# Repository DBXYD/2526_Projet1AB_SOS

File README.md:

# 2526_Projet1AB_SOS
## Introduction
### 1.1 Contexte et Problématique
Dans le cadre de la gestion logistique des laboratoires de l'ENSEA, le suivi précis et rigoureux des composants électroniques constitue un défi quotidien. Actuellement, l'inventaire repose sur un référencement manuel via un fichier Excel, et le stockage physique est réparti dans des boîtes de dimensions variables.
Ce mode de gestion présente plusieurs limites :

- Erreurs d'indexation : Risque élevé d'oublis ou de doubles saisies lors d'une mise à jour des stocks.
- Perte de traçabilité spatiale : Difficulté à localiser physiquement les boîtes suite à des déplacements ou réorganisations.
- Asynchronisme des données : Décalage temporel entre le mouvement réel d'un composant et sa mise à jour logicielle.

### 1.2 Objectifs du Projet SOS
Le projet SOS (Stock Organizer Scan) vise à concevoir un système embarqué de numérisation basé sur la technologie RFID (Radio Frequency Identification).
Chaque boîte de rangement se voit attribuer un tag RFID unique. Le dispositif SOS lit et écrit ces puces pour associer un contenant physique à ses données logistiques :
- Le MPN (Manufacturer Part Number) : référence exacte du constructeur
- SKU (Stock Keeping Unit) : code interne d'identification du stock
- LocalisationSalle précise au sein des différents tiroclasses de l'ENSEA
- Quantité exacte d'exemplaires restants

### 1.3 Solution mise en œuvre
Le projet s'articule autour de deux parties :

1) [Hardware](./Hardware) : Une carte électronique sur mesure intégrant une carte électronique sur mesure intégrant un microcontrôleur basse
consommation STM32L4, un lecteur RFID communiquant via bus SPI matériel, et une interface USB-C assurant à la fois l’alimentation et l’échange de données haut débit.

3) [Software](./Software) : Une interface utilisateur développée en Python, permettant aux techniciens d'interagir avec la base de données.

## 2. Analyse détaillée des blocs fonctionnels
Le schématique du système SOS (Stock Organizer Scan) est structuré de manière ri-
goureuse en blocs fonctionnels distincts.

### 2.1 Bloc Alimentation (Power Supply)

Ce bloc assure la conversion et la régulation de l'énergie nécessaire aux différents composants.

- Composants identifiés :
  - Régulateur LDO :  BU33SD5WG-TR (5 V → 3.3 V)
  - Condensateurs : C1 (1 μF) et C2 (1 μF)
  - Interrupteur : SW_SPDT (SW1)
  - LEDs indicatrices : D1 et D2 avec résistances associées R3 (3.4 kΩ) et R4 (1.6 kΩ)

- Justification des choix :
  - BU33SD5WG-TR : Ce régulateur (LDO) est particulièrement adapté pour abaisser le 5V issu de l’USB vers le rail 3.3 V. Son boîtier compact minimise l’empreinte au sol. De plus, sa capacité en courant ici est largement suffisante pour alimenter simultanément notre microcontrôleur STM32 et le lecteur RFID.

  - C1 et C2 (1 μF) : Placés en découplage direct sur l’entrée et la sortie du LDO conformément aux spécifications du constructeur. Ils stabilisent la tension ici.
  - SW1 (SW_SPDT) : Permet de couper l’alimentation de la carte sans avoir à débrancher physiquement le câble USB. Cela est plutôt intéressant d’un point de vue confort d’utilisation.

### 2.2 Bloc Port USB (USB-C)

L'interface USB-C gère le transfert de données et l'apport d'énergie principal.

- Composants identifiés :
  - Connecteur USB-C : J1 (Référence commerciale : 629722000214)
  - Protection ESD : U2 (USBLC6-2SC6)
  - Résistances de configuration : R1 (5.4 kΩ), R2 (5.1 kΩ) sur les lignes CC1/CC2
  - 
- Justification des choix :
  - Connecteur Molex USB-C : Nous avons opter ici pour USB-C et non un Micro-USB car
le premier est réversible et largement plus robustesse.
  - USBLC6-2SC6 : Réseau de diodes TVS bidirectionnel ultra-faible capacité dédié à la
protection des lignes D+ et D−. Cette protection est indispensable contre les décharges
électrostatiques (ESD) induites lorsque’un humaine manipule le connecteur USB manuellement.

### 2.3 Bloc STM32 (Microcontrôleur principal)

Le cœur logique du système repose sur le STM32L476RGTx (boîtier LQFP64) de STMicroelectronics. Composant central : STM32L476RGTx.

Ecosystème ENSEA : Il s’agit d’un composant sur lequel nous avons ulterieusrement eu a travaillé durant les séances de TD et TP surtout. SPI Matériel dispose de plusieurs bus SPI indépendants pour piloter à haute fréquence le lecteur RFID.

- Signaux notables :
  - SPI1_* → Liaison vers le lecteur RFID.
  - VCP_TX / VCP_RX → Interface UART pontée vers l’USB pour la communication avec le
script Python.
  - USB_DN / USB_DP → Lignes différentielles du bus USB physique.
  - SWDIO / SWCLK → Interface de programmation/débogage JTAG/SWD.
  - USR_LED_1 / USR_LED_2 → Indication d’état utilisateur (ex : scan réussi).
  - NRST / BOOT0 → Lignes de contrôle.
 
Remarque : Les condensateurs de découplage (C5 à C10, 100 nF) sont assignés individuellement à chaque broche d’alimentation VDD du STM32. Ils suppriment le bruit haute fréquence issu des commutations internes du coeur.

### 2.4 Bloc Lecteur RFID

Ce bloc gère l'acquisition des données des tags RFID attachés aux produits stockés.

- Interface SPI : Exploitation du bus à haute vitesse (jusqu’à 10 Mbit/s), réduisant la
latence lors de la lecture des identifiants.
- Compatibilité de tension : Fonctionnant sous 3.3 V, le composant fonctione directement
avec le STM32.
- Découplage local (C13,C14 - 1 μF) : Placés au plus près du circuit RFID pour pallier les
appels de courant violents générés par l’antenne lors de l’émission du champ magnétique
RF.

### 2.5 Bloc Connecteur SWD

Ce bloc offre un accès direct aux broches de débogage via une sonde externe de type ST-Link, pour le flashage et le débogage à chaud du microcontrôleur.

### 2.6 Boutons et signaux utilisateur

### 2.7 Trous de fixation (Mounting Pads)

Les quatre perçages H1 à H4 (MountingHole_Pad) garantissent la rigidité de l’intégration au sein d’un boîtier personnalisé.

## 3. Routage
Le passage du schéma théorique du [PCB](./PCB) permettant le tracé des pistes physiques impose le respect de contraintes géométriques et électromagnétiques strictes.

### 3.1 Réalisation Matérielle et Placements des blocs

La conception du circuit imprimé a abouti à une modélisation tridimensionnelle permettant de valider l’intégration mécanique des composants, l’accessibilité des connecteurs.

Le microcontrôleur STM32L476RGTx (boîtier LQFP64) occupe une position parfaitement centrale. Cette disposition permet une distribution homogène des pistes de signaux vers les différents périphériques, minimisant ainsi la longueur moyenne des pistes.

- Implantation des diffférents blocs :
  - Connecteur USB-C et Protection ESD : Placés au plus près du bord de la carte. L’alignement direct du circuit de protection TVS en entrée du connecteur garantit que les décharges électrostatiques sont immédiatement dérivées vers la masse avant de pouvoir se propager vers l’intérieur du circuit.
  - Connecteur d’extension RFID : Disposé sur la périphérie supérieure sous forme d’un connecteur femelle barrette, offrant une liaison mécanique et électrique stable pour le module MFRC522 tout en évitant les superpositions de composants.
  - Connecteur SWD (J2) : Isolé à droite afin de permettre un raccordement aisé de la sonde ST-Link lors des phases de flashage sans gêner l’accès au port USB principal.
  - Mounting Pads : la présence de quatre trous de fixation métallisés (Mounting Pads) répartis de manière symétrique aux quatre angles de la carte valide l’aptitude du prototype à être intégré de manière rigide au sein d’un boîtier de protection. L’espacement laissé libre autour de ces trous garantit le passage des têtes de vis sans risque d’écrasement ou de court-circuit sur les pistes environnantes.

## 4. Configuration des pins

Le microcontrôleur STM32L476RGTx (LQFP64) est configuré avec les affectations suivantes :

- Port A — SPI1 (NSS, SCK, MISO, MOSI), USB (DM, DP), VCP (TX, RX)
- Port B — RFID IRQ, boutons utilisateur (BTN_1, BTN_2), SWD, LEDs utilisateur
- Port C — OSC, LEDs, RFID RST
- Signaux de contrôle — NRST, BOOT0

## 5. Software
### 5.1 Firmware
La liaison entre le PC et le tag RFID à travers le PCB est gérée par du code en C, où on retrouve une séparation par composants. Le projet est construit de manière à pouvoir réutiliser des morceaux du code pour d’autres projets faisant intervenir des composants de celui-ci.\
Par la suite on détaillera seulement les fichiers contenant des fonctions écrites par nous, et non des fichiers générés par STM32CubeIDE lors de l'affectation des pins sur le .ioc (gpio, spi, usart,...).\

Dans le main.c se trouvent des appels aux fonctions d'initialisation et une boucle infinie où l'appel à test() de algo.c permet de tester des fonctionnalités en mode debuggeur.\
\
Le fichier rfid.c contient des fonctions ayant trait à la liaison SPI entre la STM32 et le lecteur RFID, et une structure permettant de définir les broches associées à un lecteur RFID. Cette dernière est initialisée grâce à la fonction RFID_init(hrfid, hspi, hspi_nss_port, hspi_nss_pin, rst_port, rst_pin). 

- void RFID_transmit(RFID_HandleTypeDef* hrfid, uint8_t* data, int size) transmet les données de data au tag et les y écrit;
- void RFID_receive(RFID_HandleTypeDef* hrfid, uint8_t* data, int size) lit les données du tag et les envoie au master en les stockant dans un buffer data.
- void RFID_transmit_receive(RFID_HandleTypeDef* hrfid, uint8_t* pTxData, uint8_t* pRxData, int size) fait les deux, l’un après l’autre.

Le fichier algo.c contient des fonctions rassemblant celles des autres fichiers, mettant ainsi bout à bout les différents éléments du PCB. Les fonctions read et write font alors intervenir le lecteur RFID et la liaison USART avec le PC. 

- void test() est utile pour la phase développement: elle aide à vérifier le fonctionnement de read(huart, hrfid, pdata, size) et write(huart, hrfid, pdata, size). On commence par lire le tag RFID, puis on y enregistre des données qu’on cherche enfin à retrouver en refaisant appel à read. 

- uint8_t SPI1_WriteRead(uint8_t data, SPI_HandleTypeDef hspi1) fait appel à RRFID_transmit_receive(hrfid, pTxData, pRxData, size). Elle est particulièrement utile dans les cas où ces deux actions doivent être effectuées l’une après l’autre. RFID_transmit_receive gère le délai de transmission. 

### 5.2 Interface Python
Pour assurer l’interface entre l’utilisateur et la carte électronique SOS, une application logicielle a été développée en Python qui était une condition nécéssaire dans notre projet. 
L’application s’appuie sur trois bibliothèques clés, assurant chacune un rôle pilier dans le traitement des données :
Le script Python s’appuie sur trois bibliothèques principales pour articuler ses différentes tâches. Elles sont structurées de la manière suivante :

- serial :
  - Rôle : Gestion de la couche de liaison série.
  - Utilité : Permet l’ouverture, la configuration et l’écoute du port COM virtuel (VCP) créé par le branchement USB-C du STM32. C’est elle qui intercepte le flux binaire.
    
- tkinter :
  - Rôle : Framework de construction d’Interface Homme-Machine (IHM).
  - Utilité : Bibliothèque standard de Python permettant de générer la fenêtre principale de l’application SOS, de positionner les boutons de contrôle et de mettre à jour dynamiquement les étiquettes de texte lors d’un scan.

- pandas :
  - Rôle : Manipulation et analyse de structures de données.
  - Utilité : Charge en mémoire le fichier tableur Excel faisant office de base de données d’inventaire de l’ENSEA. Elle permet d’effectuer des recherches indexées ultrarapides à partir d’un emplacement donné pour en extraire le MPN et le SKU.

Dans notre progremme Python, on retrouve les fonctions suivantes : 
- scan() :
  - Entrée : void
  - Rôle : Ouvre le canal de communication série USB-C avec le STM32.
  - Sortie : serial.Serial ou None : ser (instance de connexion)
- decode(data) :
  - Entrée : bytes : data
  - Rôle : Convertit les données en hexadécimal reçues en une listee de caractères utilisable.
  -Sortie : list[str,str,int,int,int] : location
- search_info(location) :
  - Entrée : list : location
  - Rôle : Requête de recherche au sein du fichier d’inventaire Excel 
  - Sortie : int : mpn, int : sku
- display_info(mpn, sku, location) :
  - Entrée : int : mpn, int : sku, list : location
  - Rôle : Met à jour dynamiquement l’interface graphique.
  - Sortie : NoneType : None
- read_data():
  - Entrée : void
  - Rôle : Suite à l'appui sur le bouton read, appelle les fonction scan, decode, search_info et display_info pour afficher SKU, MPN et localisation sur l'interface
  - Sortie : Nonetype : None
- write_loc():
  - Entrée : void
  - Rôle : demande à l'utilisateur la localisation à attribuer à la puce scannée 
  - Sortie : Nonetype : None
- display_value():
  - Entrée : void
  - Rôle : Suite à l'appui sur le bouton "done" (lorque l'utilisateur a entré la localisation et a terminé), convertit cette localisation en identifiant (locbytes) puis appelle la fonction assign_tag(loc_bytes)
  - Sortie : Nonetype : None
- assign_tag(loc_bytes):
  - Entrée : bytes loc_bytes
  - Rôle : Ouvre le canal de communication série USB-C avec le STM32 et envoie à la STM32 l'identifiant à attribuer à la puce.
  - Sortie : Nonetype : None
  
## 6. Question environnementale

A l'issue de notre projet nous avons finalement choisis la question : Votre projet recherche-t-il la rentabilité dans une perspective de viabilité financière ?

A cette question, nous y repondons *oui* et ce pour plusieurs raisons :
- **Gain de temps et d'organisation** : le système SOS permet aux techniciens de localiser instantanément les composants, réduisant les pertes de temps liées à la recherche manuelle en tiroir.
- **Économie d'argent important** : avec une actualisation automatique du système, nous pouvons éviter de recommander des composants déjà présents au sein de l'école.
- **Facilité de commande** : grâce au suivi précis des stocks (quantité, SKU, MPN), les réapprovisionnements sont déclenchés au bon moment, évitant les ruptures comme les sur-stocks inutiles.
- **"Le temps c'est de l'argent"** : chaque minute gagnée en gestion de stock est une minute réinvestie dans des tâches à plus forte valeur ajoutée.

En ce sens, le projet SOS s'inscrit pleinement dans une logique de rentabilité opérationnelle et de viabilité financière à long terme.

## Conslusion
Le projet SOS (Stock Organizer Scan) est, à ce stade, un projet en cours de développement dont on a malheuresement pas pu venir à bout. Cependant, nous avons pu faire une belle avancée : une carte électronique sur mesure intégrant un microcontrôleur STM32L4 et un lecteur RFID, couplée à une interface logicielle en Python, constitue une solution cohérente et pensée pour répondre à un besoin concret au sein de l'ENSEA.

Même inachevé, le projet démontre une réelle utilité : automatiser le suivi des composants électroniques, réduire les erreurs de gestion de stock et faciliter les commandes sont des apports directs pour les techniciens et les étudiants qui utilisent les tiroclasses au quotidien.

Ce projet nous a également permis de monter en compétences sur des technologies variées : conception PCB, communication SPI, développement logiciel et gestion de projet en équipe. Il constitue une base que d'autres promotions pourraient reprendre et faire évoluer vers un système pleinement opérationnel.

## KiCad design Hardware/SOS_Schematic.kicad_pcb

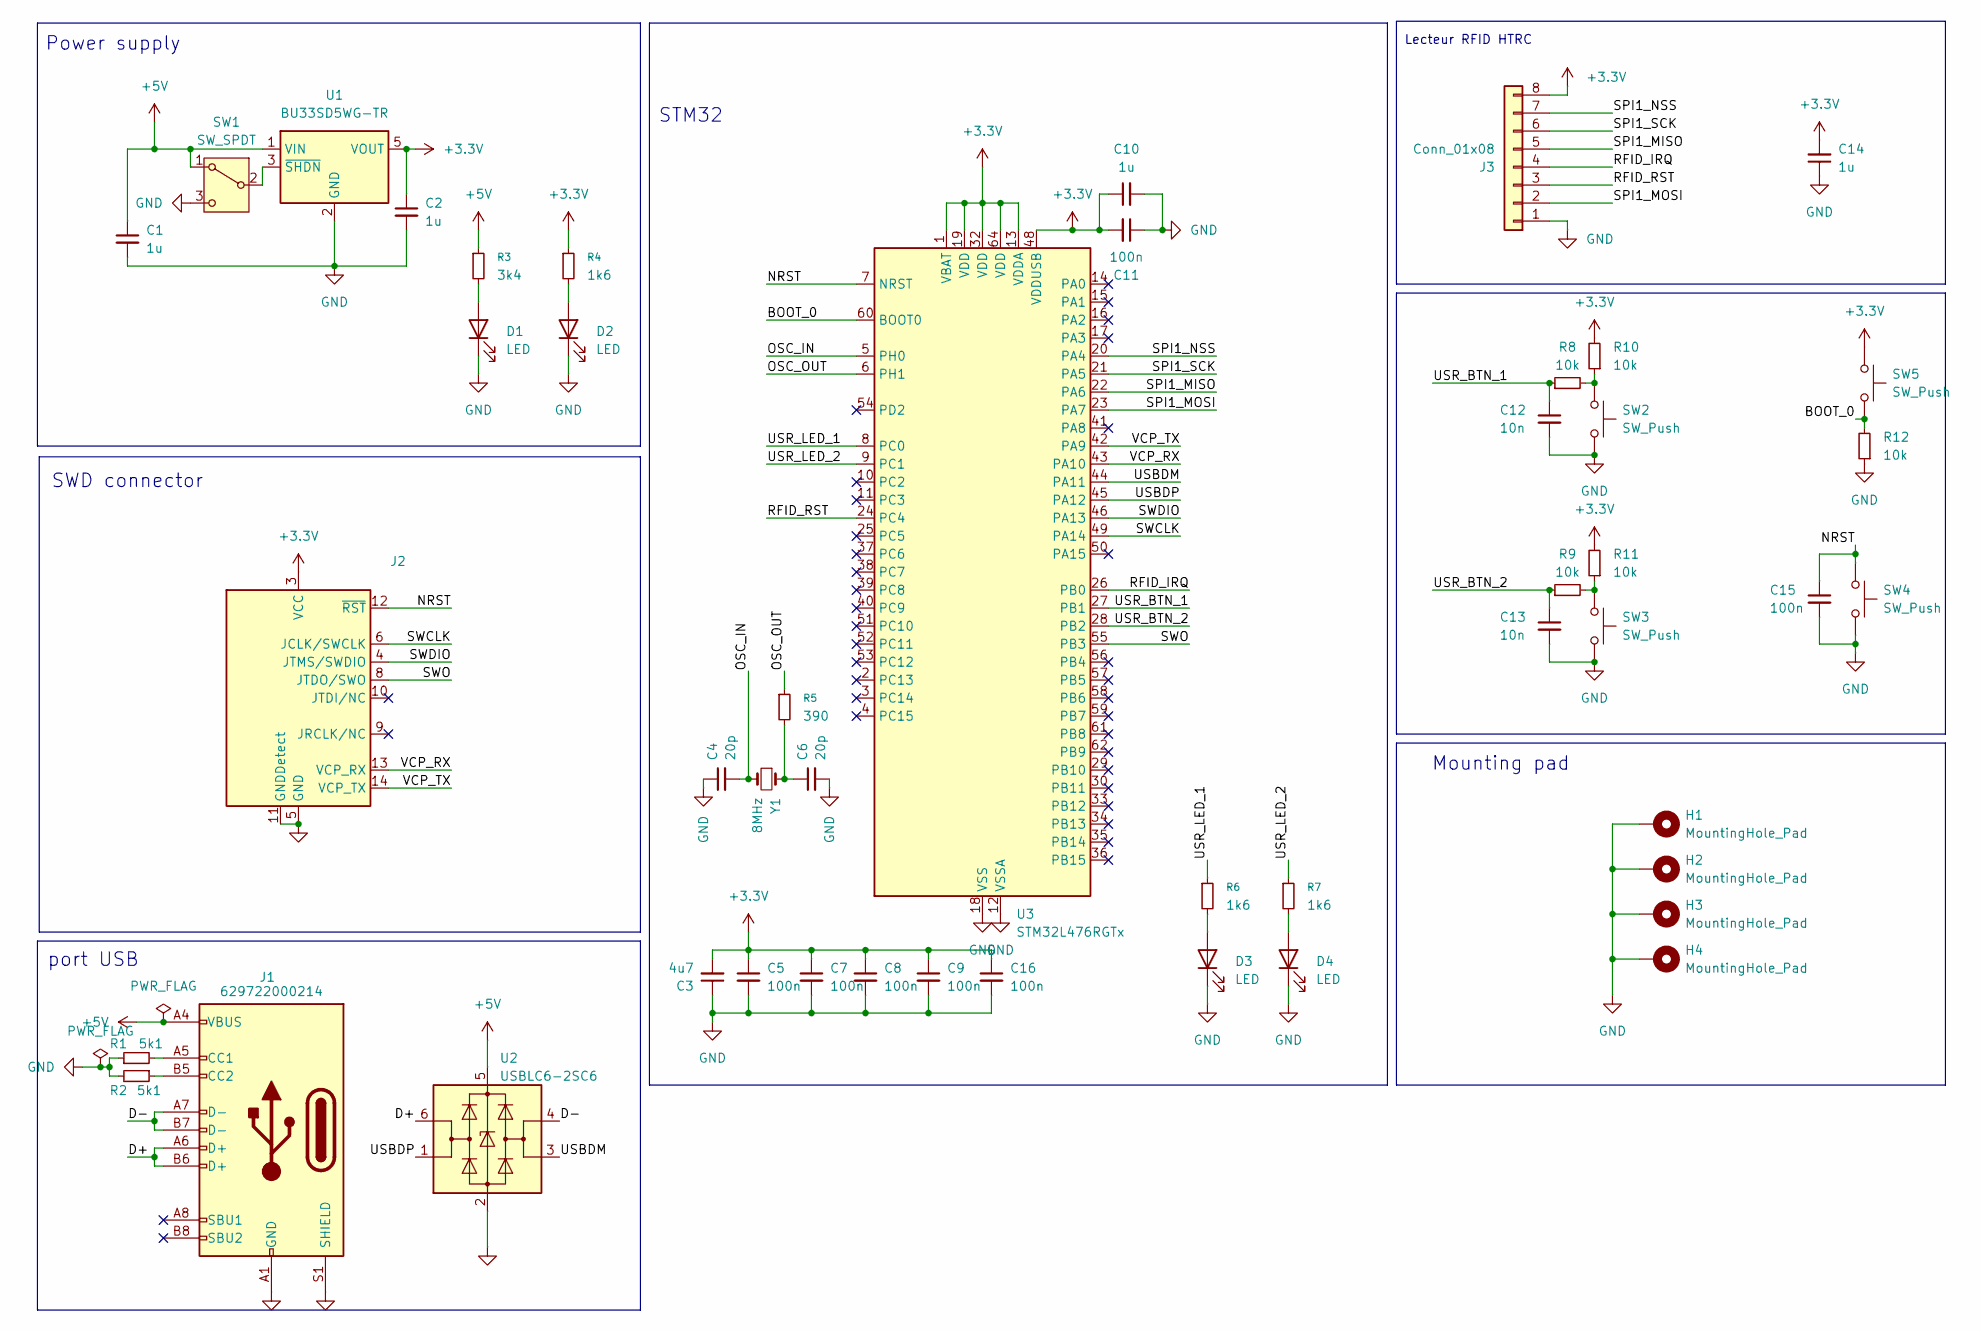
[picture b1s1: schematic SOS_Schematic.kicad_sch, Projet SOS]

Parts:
C1, C2, C10, C14: 1u; C_0402_1005Metric
C3: 4u7; C_0603_1608Metric
C4, C6: 20p; C_0402_1005Metric
C5, C7, C8, C9, C11, C15, C16: 100n; C_0402_1005Metric
C12, C13: 10n; C_0402_1005Metric
D1, D2, D3, D4: LED; LED_0603_1608Metric; MPN 150060RS55040
H1, H2, H3, H4: MountingHole_Pad; MountingHole_3.2mm_M3_DIN965_Pad
J1: 629722000214; USB_C_Receptacle_HRO_TYPE-C-31-M-12; MPN WE 629722000214
J2: PinHeader_2x07_P1.27mm_Vertical_SMD
J3: Conn_01x08; PinSocket_1x08_P2.54mm_Vertical
R1, R2: 5k1; R_0402_1005Metric
R3: 3k4; R_0402_1005Metric
R4, R6, R7: 1k6; R_0402_1005Metric
R5: 390; R_0402_1005Metric
R8, R9, R10, R11, R12: 10k; R_0402_1005Metric
SW1: SW_SPDT; SW_SPDT_CK_JS102011SAQN
SW2, SW3, SW4, SW5: SW_Push; SW_SPST_CK_KMS2xxG; MPN KSS221GLFS
U1: BU33SD5WG-TR; SOT-23-5
U2: USBLC6-2SC6; SOT-23-6; MPN USBLC6-2SC6
U3: STM32L476RGTx; LQFP-64_10x10mm_P0.5mm
Y1: 8MHz; Crystal_SMD_Abracon_ABM7-2Pin_6.0x3.5mm

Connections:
+3.3V: C2.1, C3.2, C5.1, C7.1, C8.1, C9.1, C10.1, C11.2, C14.2, C16.1, J2.3 (VCC), J3.8, R4.1, R10.2, R11.2, SW5.1, U1.5 (VOUT), U3.1 (VBAT), U3.13 (VDDA), U3.19 (VDD), U3.32 (VDD), U3.48 (VDDUSB), U3.64 (VDD)
+5V: C1.1, J1.A4 (VBUS), J1.A9 (VBUS), J1.B4 (VBUS), J1.B9 (VBUS), R3.1, SW1.1 (A), U1.1 (VIN), U2.5 (VBUS)
/BOOT_0: R12.2, SW5.2, U3.60 (BOOT0)
/D+: J1.A6 (D+), J1.B6 (D+), U2.6 (I/O1)
/D-: J1.A7 (D-), J1.B7 (D-), U2.4 (I/O2)
/NRST: C15.1, J2.12 (~RST), SW4.1, U3.7 (NRST)
/OSC_IN: C4.2, U3.5 (PH0), Y1.2
/OSC_OUT: R5.1, U3.6 (PH1)
/RFID_IRQ: J3.4, U3.26 (PB0)
/RFID_RST: J3.3, U3.24 (PC4)
/SPI1_MISO: J3.5, U3.22 (PA6)
/SPI1_MOSI: J3.2, U3.23 (PA7)
/SPI1_NSS: J3.7, U3.20 (PA4)
/SPI1_SCK: J3.6, U3.21 (PA5)
/SWCLK: J2.6 (JCLK/SWCLK), U3.49 (PA14)
/SWDIO: J2.4 (JTMS/SWDIO), U3.46 (PA13)
/SWO: J2.8 (JTDO/SWO), U3.55 (PB3)
/USBDM: U2.3 (I/O2), U3.44 (PA11)
/USBDP: U2.1 (I/O1), U3.45 (PA12)
/USR_BTN_1: C12.1, R8.1, U3.27 (PB1)
/USR_BTN_2: C13.1, R9.1, U3.28 (PB2)
/USR_LED_1: R6.1, U3.8 (PC0)
/USR_LED_2: R7.1, U3.9 (PC1)
/VCP_RX: J2.13 (VCP_RX), U3.43 (PA10)
/VCP_TX: J2.14 (VCP_TX), U3.42 (PA9)
GND: C1.2, C2.2, C3.1, C4.1, C5.2, C6.2, C7.2, C8.2, C9.2, C10.2, C11.1, C12.2, C13.2, C14.1, C15.2, C16.2, D1.1 (K), D2.1 (K), D3.1 (K), D4.1 (K), H1.1 (1_1), H2.1 (1_1), H3.1 (1_1), H4.1 (1_1), J1.A1 (GND), J1.A12 (GND), J1.B1 (GND), J1.B12 (GND), J1.S1 (SHIELD), J2.5 (GND), J2.7 (GND), J2.11 (GNDDetect), J3.1, R1.1, R2.2, R12.1, SW1.3 (C), SW2.2, SW3.2, SW4.2, U1.2 (GND), U2.2 (GND), U3.12 (VSSA), U3.18 (VSS), U3.31 (VSS), U3.47 (VSS), U3.63 (VSS)
unnamed: C6.1, R5.2, Y1.1
unnamed: D1.2 (A), R3.2
unnamed: D2.2 (A), R4.2
unnamed: D3.2 (A), R6.2
unnamed: D4.2 (A), R7.2
unnamed: J1.A5 (CC1), R1.2
unnamed: J1.B5 (CC2), R2.1
unnamed: R8.2, R10.1, SW2.1
unnamed: R9.2, R11.1, SW3.1
unnamed: SW1.2 (B), U1.3 (~SHDN)

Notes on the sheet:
STM32
Power supply
Mounting pad
SWD connector
Lecteur RFID HTRC
port USB

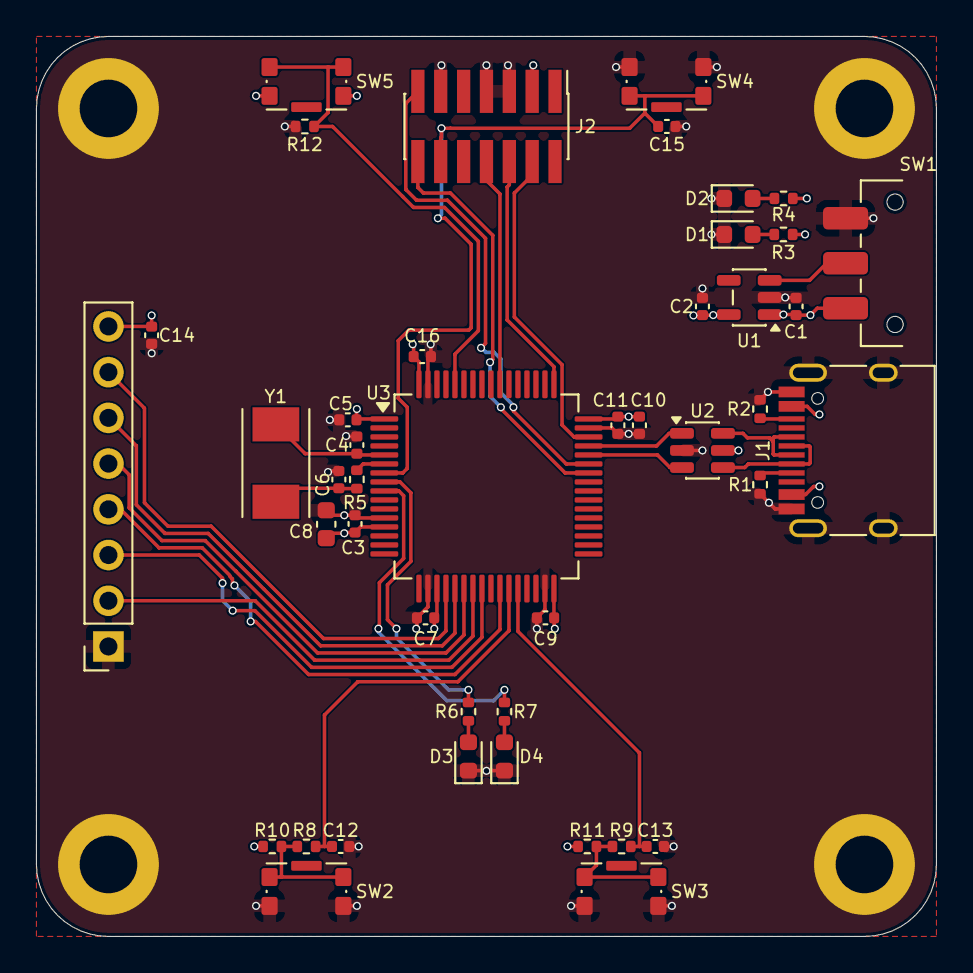
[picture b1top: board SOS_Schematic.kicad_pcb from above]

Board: 4 copper layers, 50.0 x 50.0 mm, 48 parts (0 on the bottom side), 36 nets.

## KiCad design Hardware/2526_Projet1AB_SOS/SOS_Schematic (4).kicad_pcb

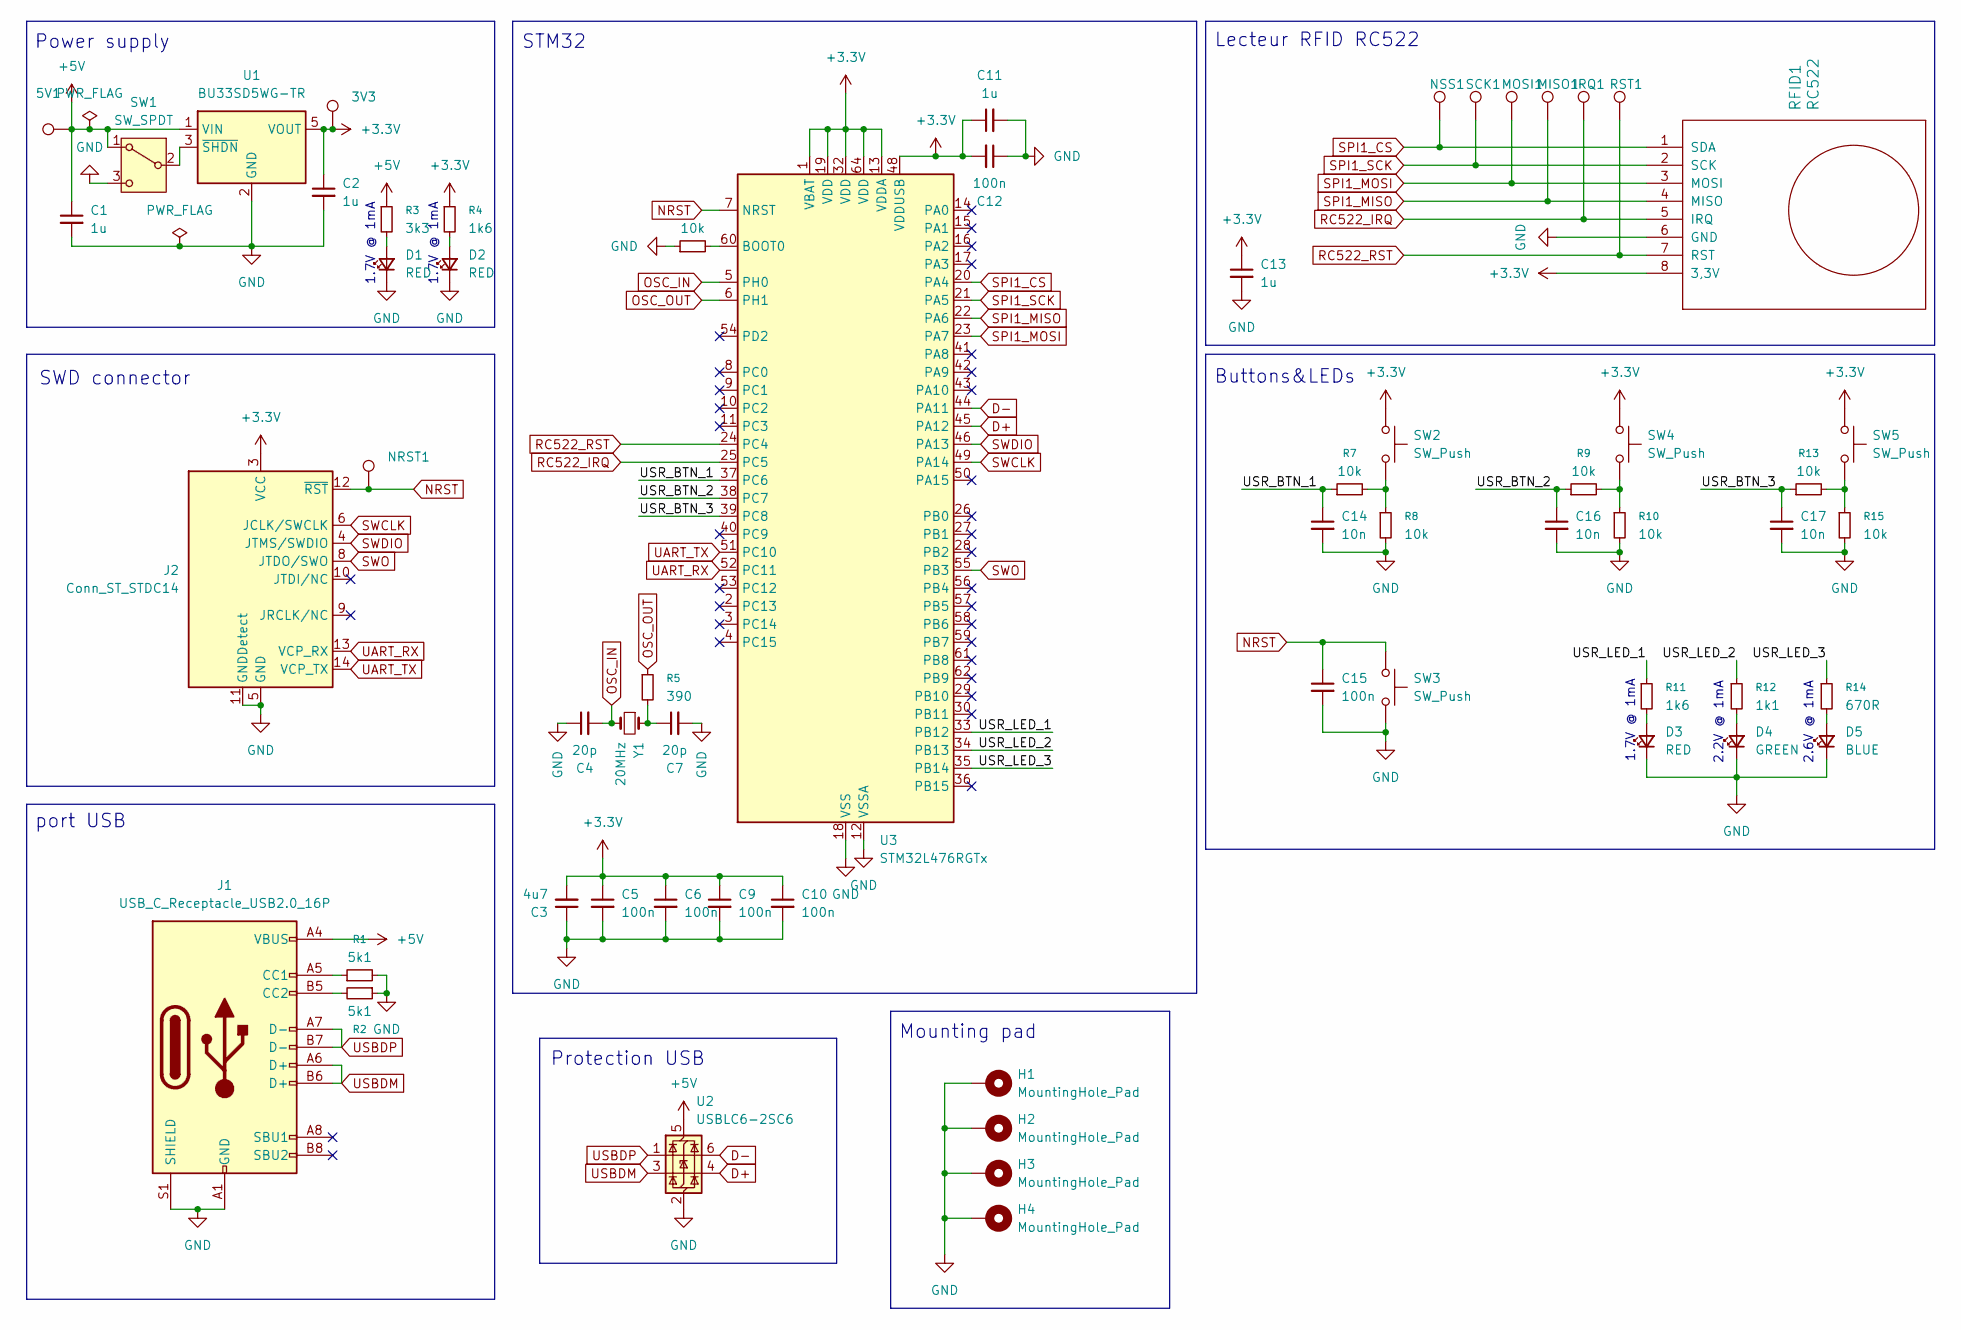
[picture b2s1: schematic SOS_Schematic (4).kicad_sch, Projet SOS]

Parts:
3V3, 5V1: TestPoint; TestPoint_Pad_D1.0mm
C1, C2, C11, C13: 1u; C_0603_1608Metric
C3: 4u7; C_0603_1608Metric
C4, C7: 20p; C_0603_1608Metric
C5, C6, C9, C10, C12, C15: 100n; C_0603_1608Metric
C14, C16, C17: 10n; C_0603_1608Metric
D1, D2, D3: RED; LED_0603_1608Metric; MPN 150060RS55040
D4: GREEN; LED_0603_1608Metric; MPN 150060GS55040
D5: BLUE; LED_0603_1608Metric; MPN 150060BS55040
H1, H2, H3, H4: MountingHole_Pad; MountingHole_3.2mm_M3_Pad
IRQ1: TestPoint; TestPoint_Pad_D1.0mm
J1: USB_C_Receptacle_USB2.0_16P; USB_C_Receptacle_GCT_USB4105-xx-A_16P_TopMnt_Horizontal
J2: Conn_ST_STDC14; PinHeader_2x07_P1.27mm_Vertical_SMD
MISO1: TestPoint; TestPoint_Pad_D1.0mm
MOSI1: TestPoint; TestPoint_Pad_D1.0mm
NRST1: TestPoint; TestPoint_Pad_D1.0mm
NSS1: TestPoint; TestPoint_Pad_D1.0mm
R1, R2: 5k1; R_0603_1608Metric
R3: 3k3; R_0603_1608Metric
R4, R11: 1k6; R_0603_1608Metric
R5: 390; R_0603_1608Metric
R6, R7, R8, R9, R10, R13, R15: 10k; R_0603_1608Metric
R12: 1k1; R_0603_1608Metric
R14: 670R; R_0603_1608Metric
RFID1: RC522; PinSocket_1x08_P2.54mm_Vertical
RST1: TestPoint; TestPoint_Pad_D1.0mm
SCK1: TestPoint; TestPoint_Pad_D1.0mm
SW1: SW_SPDT; SW_Push_1P2T_Vertical_E-Switch_800UDP8P1A1M6
SW2, SW3, SW4, SW5: SW_Push; SW_SPST_B3S-1000
U1: BU33SD5WG-TR; SOT-23-5
U2: USBLC6-2SC6; SOT-23-6
U3: STM32L476RGTx; LQFP-64_10x10mm_P0.5mm
Y1: 20MHz; Crystal_SMD_HC49-SD; MPN ABLS-16.000MHZ-20-B-3-H-T

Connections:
+3.3V: 3V3.1, C2.1, C3.2, C5.1, C6.1, C9.1, C10.1, C11.1, C12.2, C13.1, J2.3 (VCC), R4.1, RFID1.8 (3,3V), SW2.1, SW4.1, SW5.1, U1.5 (VOUT), U3.1 (VBAT), U3.13 (VDDA), U3.19 (VDD), U3.32 (VDD), U3.48 (VDDUSB), U3.64 (VDD)
+5V: 5V1.1, C1.1, J1.A4 (VBUS), J1.A9 (VBUS), J1.B4 (VBUS), J1.B9 (VBUS), R3.1, SW1.1 (A), U1.1 (VIN), U2.5 (VBUS)
/USR_BTN_1: C14.1, R7.1, U3.37 (PC6)
/USR_BTN_2: C16.1, R9.1, U3.38 (PC7)
/USR_BTN_3: C17.1, R13.1, U3.39 (PC8)
/USR_LED_1: R11.1, U3.33 (PB12)
/USR_LED_2: R12.1, U3.34 (PB13)
/USR_LED_3: R14.1, U3.35 (PB14)
D+: U2.4 (I/O2), U3.45 (PA12)
D-: U2.6 (I/O1), U3.44 (PA11)
GND: C1.2, C2.2, C3.1, C4.1, C5.2, C6.2, C7.2, C9.2, C10.2, C11.2, C12.1, C13.2, C14.2, C15.2, C16.2, C17.2, D1.1 (K), D2.1 (K), D3.1 (K), D4.1 (K), D5.1 (K), H1.1, H2.1, H3.1, H4.1, J1.A1 (GND), J1.A12 (GND), J1.B1 (GND), J1.B12 (GND), J1.S1 (SHIELD), J2.5 (GND), J2.7 (GND), J2.11 (GNDDetect), R1.2, R2.1, R6.1, R8.2, R10.2, R15.2, RFID1.6 (GND), SW1.3 (C), SW3.2, U1.2 (GND), U2.2 (GND), U3.12 (VSSA), U3.18 (VSS), U3.31 (VSS), U3.47 (VSS), U3.63 (VSS)
NRST: C15.1, J2.12 (~RST), NRST1.1, SW3.1, U3.7 (NRST)
unnamed: C7.1, R5.2, Y1.1
unnamed: D1.2 (A), R3.2
unnamed: D2.2 (A), R4.2
unnamed: D3.2 (A), R11.2
unnamed: D4.2 (A), R12.2
unnamed: D5.2 (A), R14.2
unnamed: J1.A5 (CC1), R1.1
unnamed: J1.B5 (CC2), R2.2
unnamed: R7.2, R8.1, SW2.2
unnamed: R9.2, R10.1, SW4.2
unnamed: R13.2, R15.1, SW5.2
unnamed: SW1.2 (B), U1.3 (~SHDN)
unnamed: R6.2, U3.60 (BOOT0)
OSC_IN: C4.2, U3.5 (PH0), Y1.2
OSC_OUT: R5.1, U3.6 (PH1)
RC522_IRQ: IRQ1.1, RFID1.5 (IRQ), U3.25 (PC5)
RC522_RST: RFID1.7 (RST), RST1.1, U3.24 (PC4)
SPI1_CS: NSS1.1, RFID1.1 (SDA), U3.20 (PA4)
SPI1_MISO: MISO1.1, RFID1.4 (MISO), U3.22 (PA6)
SPI1_MOSI: MOSI1.1, RFID1.3 (MOSI), U3.23 (PA7)
SPI1_SCK: RFID1.2 (SCK), SCK1.1, U3.21 (PA5)
SWCLK: J2.6 (JCLK/SWCLK), U3.49 (PA14)
SWDIO: J2.4 (JTMS/SWDIO), U3.46 (PA13)
SWO: J2.8 (JTDO/SWO), U3.55 (PB3)
UART_RX: J2.13 (VCP_RX), U3.52 (PC11)
UART_TX: J2.14 (VCP_TX), U3.51 (PC10)
USBDM: J1.A6 (D+), J1.B6 (D+), U2.3 (I/O2)
USBDP: J1.A7 (D-), J1.B7 (D-), U2.1 (I/O1)

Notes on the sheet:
1.7V @ 1mA
Buttons&LEDs
Protection USB
STM32
Power supply
2.6V @ 1mA
Mounting pad
SWD connector
2.2V @ 1mA
Lecteur RFID RC522
port USB

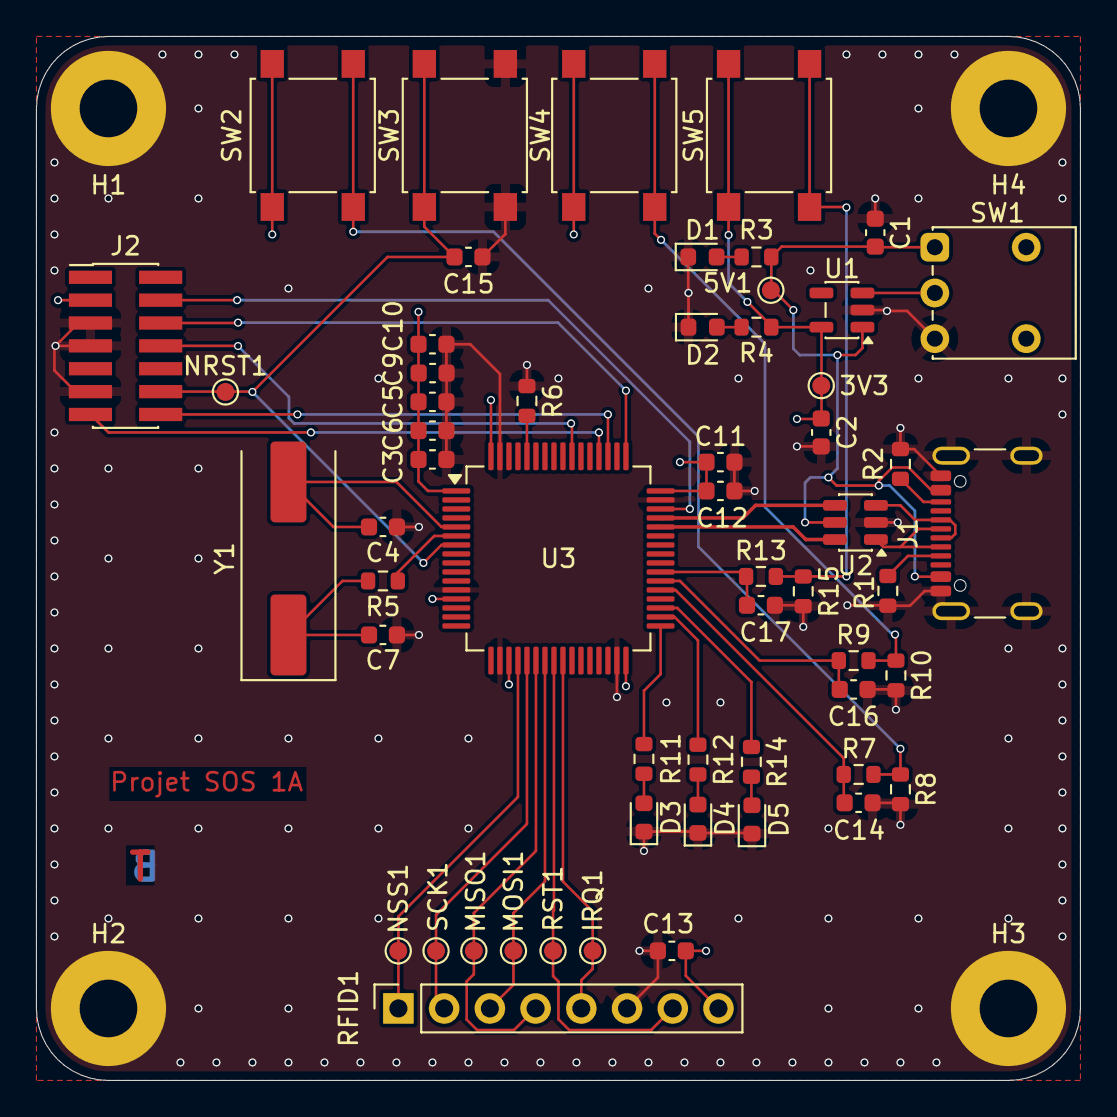
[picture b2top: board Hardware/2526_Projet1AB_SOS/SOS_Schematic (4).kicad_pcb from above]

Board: 4 copper layers, 58.0 x 58.0 mm, 61 parts (0 on the bottom side), 40 nets.

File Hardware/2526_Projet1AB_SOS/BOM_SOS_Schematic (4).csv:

"Reference","Qty","Value","DNP","Exclude from BOM","Exclude from Board","Footprint","Datasheet","Description","MPN"
"C1,C2,C11,C13","4","1u","","","","Capacitor_SMD:C_0603_1608Metric","~","Unpolarized capacitor, small symbol",""
"C3","1","4u7","","","","Capacitor_SMD:C_0603_1608Metric","~","Unpolarized capacitor, small symbol",""
"C4,C7","2","20p","","","","Capacitor_SMD:C_0603_1608Metric","~","Unpolarized capacitor, small symbol",""
"C5,C6,C9,C10,C12,C15","6","100n","","","","Capacitor_SMD:C_0603_1608Metric","~","Unpolarized capacitor, small symbol",""
"C14,C16,C17","3","10n","","","","Capacitor_SMD:C_0603_1608Metric","~","Unpolarized capacitor, small symbol",""
"D1,D2,D3","3","RED","","","","LED_SMD:LED_0603_1608Metric","https://www.we-online.com/components/products/datasheet/1500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","Light emitting diode, small symbol","150060RS55040"
"D4","1","GREEN","","","","LED_SMD:LED_0603_1608Metric","https://www.we-online.com/components/products/datasheet/1500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","Light emitting diode, small symbol","150060GS55040"
"D5","1","BLUE","","","","LED_SMD:LED_0603_1608Metric","~","Light emitting diode, small symbol","150060BS55040"
"H1,H2,H3,H4","4","MountingHole_Pad","","","","MountingHole:MountingHole_3.2mm_M3_Pad","~","Mounting Hole with connection",""
"J1","1","USB_C_Receptacle_USB2.0_16P","","","","","https://www.usb.org/sites/default/files/documents/usb_type-c.zip","USB 2.0-only 16P Type-C Receptacle connector",""
"J2","1","Conn_ST_STDC14","","","","Connector_PinHeader_1.27mm:PinHeader_2x07_P1.27mm_Vertical_SMD","https://www.st.com/content/ccc/resource/technical/document/u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","ST Debug Connector, standard ARM Cortex-M SWD and JTAG interface plus UART",""
"R1,R2","2","5k1","","","","Resistor_SMD:R_0603_1608Metric","~","Resistor, small symbol",""
"R3","1","3k3","","","","Resistor_SMD:R_0603_1608Metric","~","Resistor, small symbol",""
"R4,R11","2","1k6","","","","Resistor_SMD:R_0603_1608Metric","~","Resistor, small symbol",""
"R5","1","390","","","","Resistor_SMD:R_0603_1608Metric","~","Resistor, small symbol",""
"R6,R7,R8,R9,R10,R13,R15","7","10k","","","","Resistor_SMD:R_0603_1608Metric","~","Resistor, small symbol",""
"R12","1","1k1","","","","Resistor_SMD:R_0603_1608Metric","~","Resistor, small symbol",""
"R14","1","670R","","","","Resistor_SMD:R_0603_1608Metric","~","Resistor, small symbol",""
"RFID1","1","RC522","","","","Connector_PinSocket_2.54mm:PinSocket_1x08_P2.54mm_Vertical","","",""
"SW1","1","SW_SPDT","","","","Button_Switch_THT:SW_Push_1P2T_Vertical_E-Switch_800UDP8P1A1M6","~","Switch, single pole double throw",""
"SW2,SW3,SW4,SW5","4","SW_Push","","","","Button_Switch_SMD:SW_SPST_B3S-1000","~","Push button switch, generic, two pins",""
"TP_3V3,TP_5V1,TP_IRQ1,TP_MISO1,TP_MOSI1,TP_NRST1,TP_NSS1,TP_RST1,TP_SCK1","9","TestPoint","","","","TestPoint:TestPoint_Pad_D1.0mm","~","test point",""
"U1","1","BU33SD5WG-TR","","","","Package_TO_SOT_SMD:SOT-23-5","http://ww1.microchip.com/downloads/en/DeviceDoc/22053C.pdf","150mA, Tiny CMOS LDO With Shutdown, Fixed Voltage, SOT-23-5",""
"U2","1","USBLC6-2SC6","","","","Package_TO_SOT_SMD:SOT-23-6","https://www.st.com/resource/en/datasheet/usblc6-2.pdf","Very low capacitance ESD protection diode, 2 data-line, SOT-23-6",""
"U3","1","STM32L476RGTx","","","","Package_QFP:LQFP-64_10x10mm_P0.5mm","https://www.st.com/resource/en/datasheet/stm32l476rg.pdf","STMicroelectronics Arm Cortex-M4 MCU, 1024KB flash, 128KB RAM, 80 MHz, 1.71-3.6V, 51 GPIO, LQFP64",""
"Y1","1","20MHz","","","","Crystal:Crystal_SMD_HC49-SD","~","Two pin crystal, small symbol","ABLS-16.000MHZ-20-B-3-H-T"

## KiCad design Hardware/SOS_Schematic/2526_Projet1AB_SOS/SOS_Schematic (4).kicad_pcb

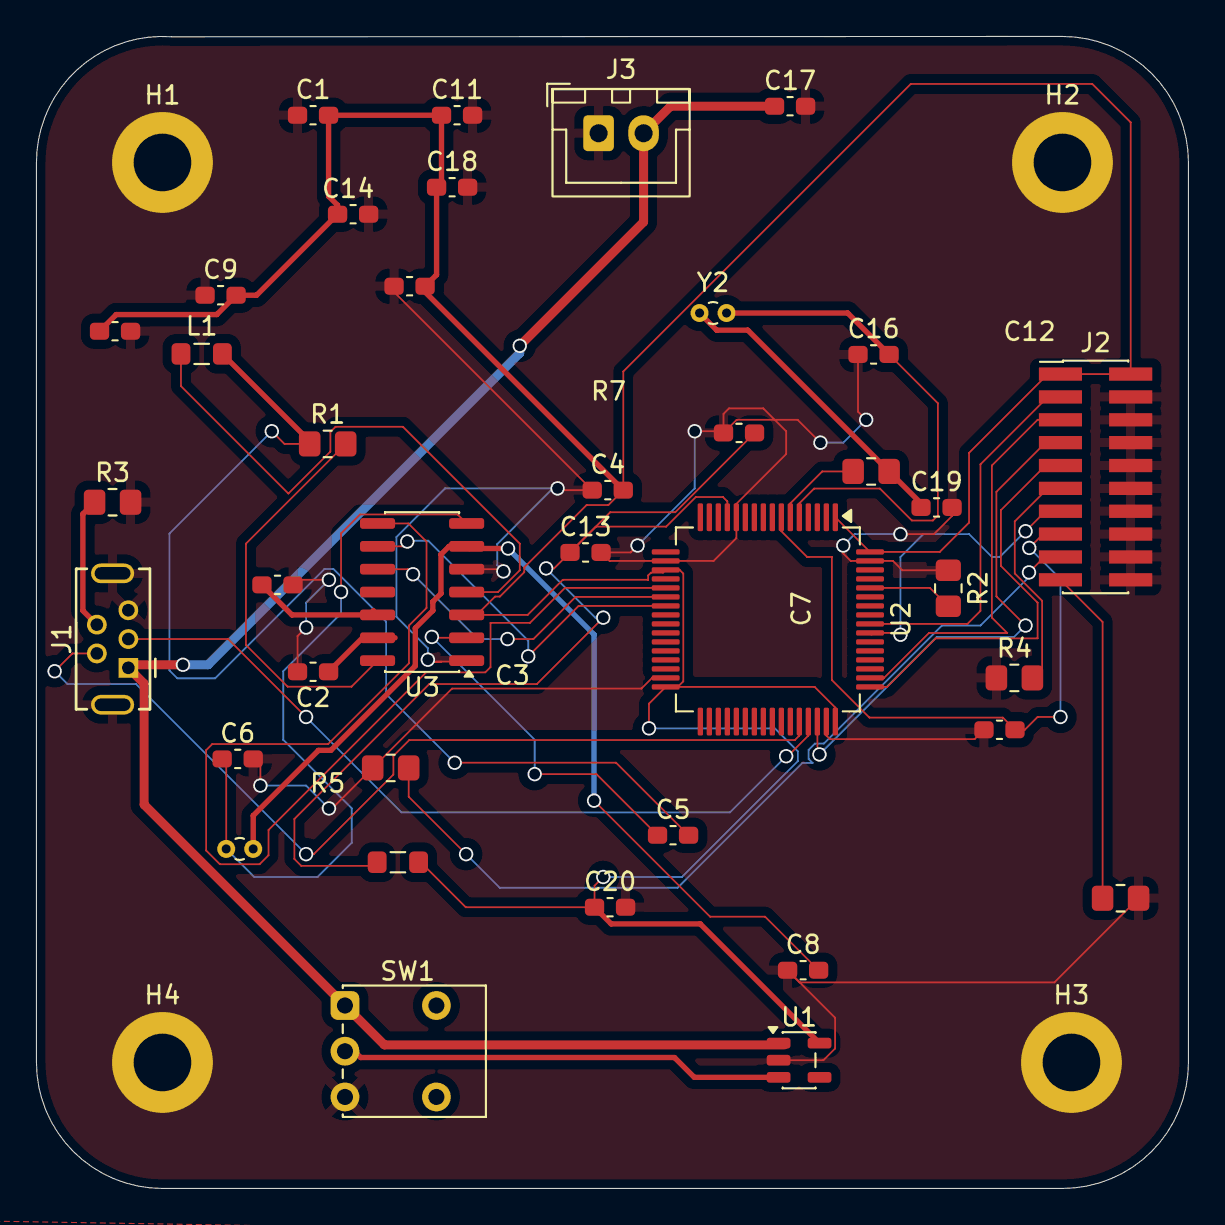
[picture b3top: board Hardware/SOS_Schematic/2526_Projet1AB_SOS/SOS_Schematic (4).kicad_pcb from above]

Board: 2 copper layers, 64.0 x 64.0 mm, 42 parts (0 on the bottom side), 32 nets.

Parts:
C1, C2, C3, C7, C10, C11, C14, C15: 100n; C_0603_1608Metric_Pad1.08x0.95mm_HandSolder
C4: 10u; C_0603_1608Metric_Pad1.08x0.95mm_HandSolder
C5: 1,5n; C_0603_1608Metric_Pad1.08x0.95mm_HandSolder
C6, C8: 22p; C_0603_1608Metric_Pad1.08x0.95mm_HandSolder
C9: 4,7u; C_0603_1608Metric_Pad1.08x0.95mm_HandSolder
C12: 10n; C_0603_1608Metric_Pad1.08x0.95mm_HandSolder
C13, C17, C18, C20: 1u; C_0603_1608Metric_Pad1.08x0.95mm_HandSolder
C16, C19: 20p; C_0603_1608Metric_Pad1.08x0.95mm_HandSolder
H1, H2, H3, H4: MountingHole_Pad; MountingHole_3.2mm_M3_DIN965_Pad
J1: USB_B_Mini; USB_Mini-B_Tensility_54-00023_Vertical
J2: Conn_02x10_Odd_Even; PinHeader_2x10_P1.27mm_Vertical_SMD
J3: Conn_01x02; JST_XH_B2B-XH-A_1x02_P2.50mm_Vertical
L1: 1/2 uH; L_0805_2012Metric_Pad1.05x1.20mm_HandSolder
L2: L_Small; L_0805_2012Metric_Pad1.05x1.20mm_HandSolder
R1: 2,2k; R_0805_2012Metric_Pad1.20x1.40mm_HandSolder
R2, R4, R5, R6: 10k; R_0805_2012Metric_Pad1.20x1.40mm_HandSolder
R3: 100K; R_0805_2012Metric_Pad1.20x1.40mm_HandSolder
R7: 390; R_0805_2012Metric_Pad1.20x1.40mm_HandSolder
SW1: SW_SPDT; SW_Push_1P2T_Vertical_E-Switch_800UDP8P1A1M6
U1: BU33SD5WG-TR; SOT-23-5
U2: STM32L476RGTx; LQFP-64_10x10mm_P0.5mm
U3: HTRC11001T; SOIC-14_3.9x8.7mm_P1.27mm
Y1: 13,56MHz; Crystal_DS10_D1.0mm_L4.3mm_Vertical
Y2: 8MHz; Crystal_DS10_D1.0mm_L4.3mm_Vertical

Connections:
+3.3V: C1.2, C4.2, C9.2, C10.1, C11.1, C14.1, C15.2, C18.1, C20.1, J2.1, J2.2, L2.2, U1.5 (VOUT), U2.1 (VBAT), U2.19 (VDD), U2.32 (VDD), U2.48 (VDDUSB), U2.64 (VDD), U3.3 (VDD)
+3.3VA: C12.2, C13.1, L2.1, U2.13 (VDDA)
+5V: C17.1, J1.1 (VBUS), J3.2, SW1.1 (A), U1.1 (VIN)
GND: C1.1, C2.2, C3.2, C4.1, C6.2, C7.1, C8.1, C9.1, C10.2, C11.2, C12.1, C13.2, C14.2, C15.1, C16.1, C17.2, C18.2, C19.2, C20.2, H1.1, H2.1, H3.1, H4.1, J1.5 (GND), J1.6 (Shield), J2.4, J2.6, J2.8, J2.10, J2.12, J2.14, J2.16, J2.18, J2.20, J3.1, R2.1, R3.2, R4.1, R5.1, R6.2, SW1.3 (C), U1.2 (GND), U2.12 (VSSA), U2.18 (VSS), U2.31 (VSS), U2.47 (VSS), U2.63 (VSS), U3.1 (VSS), U3.5 (MODE)
NRST: C7.2, J2.15, U2.7 (NRST)
unnamed: C5.2, L1.2, R1.1
unnamed: C19.1, R7.2, Y2.1
unnamed: J1.4 (ID), R3.1
unnamed: J2.11, R4.2
unnamed: J2.17, R5.2
unnamed: J2.19, R6.1
unnamed: SW1.2 (B), U1.3 (~SHDN)
unnamed: R2.2, U2.60 (BOOT0)
unnamed: C3.1, U3.12 (CEXT)
unnamed: C2.1, U3.13 (QGND)
unnamed: R1.2, U3.14 (RX)
unnamed: L1.1, U3.4 (TX1)
unnamed: C5.1, U3.2 (TX2)
unnamed: C8.2, U3.6 (XTAL1), Y1.2
unnamed: C6.1, U3.7 (XTAL2), Y1.1
OSC_IN: C16.2, U2.5 (PH0), Y2.2
OSC_OUT: R7.1, U2.6 (PH1)
SPI1_MISO: U2.22 (PA6), U3.10 (DOUT)
SPI1_MOSI: U2.23 (PA7), U3.9 (DIN)
SPI1_SCK: U2.21 (PA5), U3.8 (SCLK)
SWDCK: J2.9, U2.49 (PA14)
SWDIO: J2.7, U2.46 (PA13)
TDI: J2.5, U2.50 (PA15)
TDO: J2.13, U2.55 (PB3)
TRST: J2.3, U2.56 (PB4)
USBDM: J1.2 (D-), U2.44 (PA11)
USBDP: J1.3 (D+), U2.45 (PA12)

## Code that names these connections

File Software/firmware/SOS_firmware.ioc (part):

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Mcu.Name=STM32L476R(C-E-G)Tx
Mcu.Package=LQFP64
Mcu.UserName=STM32L476RGTx
PA10.Mode=Asynchronous
PA10.Signal=USART1_RX
PA11.Mode=Device_Only
PA11.Signal=USB_OTG_FS_DM
PA12.Mode=Device_Only
PA12.Signal=USB_OTG_FS_DP
PA13\ (JTMS-SWDIO).Mode=Trace_Asynchronous_SW
PA13\ (JTMS-SWDIO).Signal=SYS_JTMS-SWDIO
PA14\ (JTCK-SWCLK).Mode=Trace_Asynchronous_SW
PA14\ (JTCK-SWCLK).Signal=SYS_JTCK-SWCLK
PA2.Mode=Asynchronous
PA2.Signal=USART2_TX
PA3.Mode=Asynchronous
PA3.Signal=USART2_RX
PA4.GPIOParameters=GPIO_Label
PA4.GPIO_Label=SPI1_NSS
PA4.Signal=GPIO_Output
PA5.Mode=Full_Duplex_Master
PA5.Signal=SPI1_SCK
PA6.Mode=Full_Duplex_Master
PA6.Signal=SPI1_MISO
PA7.Mode=Full_Duplex_Master
PA7.Signal=SPI1_MOSI
PA9.Mode=Asynchronous
PA9.Signal=USART1_TX
PB0.GPIOParameters=GPIO_Label
PB0.GPIO_Label=RFID_IRQ
PB0.Signal=GPXTI0
PB1.GPIOParameters=GPIO_Label
PB1.GPIO_Label=USR_BTN_1
PB1.Signal=GPXTI1
PB2.GPIOParameters=GPIO_Label
PB2.GPIO_Label=USR_BTN_2
PB2.Signal=GPXTI2
PB3\ (JTDO-TRACESWO).Mode=Trace_Asynchronous_SW
PB3\ (JTDO-TRACESWO).Signal=SYS_JTDO-SWO
PC0.GPIOParameters=GPIO_Label
PC0.GPIO_Label=USR_LED_1
PC0.Signal=GPIO_Output
PC1.GPIOParameters=GPIO_Label
PC1.GPIO_Label=USR_LED_2
PC1.Signal=GPIO_Output
PC4.GPIOParameters=GPIO_Label
PC4.GPIO_Label=RFID_RST
PC4.Signal=GPIO_Output
PH0-OSC_IN\ (PH0).Mode=HSE-External-Oscillator
PH0-OSC_IN\ (PH0).Signal=RCC_OSC_IN
PH1-OSC_OUT\ (PH1).Mode=HSE-External-Oscillator
PH1-OSC_OUT\ (PH1).Signal=RCC_OSC_OUT
RCC.HSE_VALUE=8000000
RCC.SYSCLKFreq_VALUE=80000000
RCC.SYSCLKSource=RCC_SYSCLKSOURCE_PLLCLK
board=custom

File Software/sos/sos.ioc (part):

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Mcu.Name=STM32L476R(C-E-G)Tx
Mcu.Package=LQFP64
Mcu.UserName=STM32L476RGTx
PA11.Signal=USB_OTG_FS_DM
PA12.Signal=USB_OTG_FS_DP
PA13\ (JTMS-SWDIO).GPIOParameters=GPIO_Label
PA13\ (JTMS-SWDIO).GPIO_Label=TMS
PA13\ (JTMS-SWDIO).Mode=Trace_Asynchronous_SW
PA13\ (JTMS-SWDIO).Signal=SYS_JTMS-SWDIO
PA14\ (JTCK-SWCLK).GPIOParameters=GPIO_Label
PA14\ (JTCK-SWCLK).GPIO_Label=TCK
PA14\ (JTCK-SWCLK).Mode=Trace_Asynchronous_SW
PA14\ (JTCK-SWCLK).Signal=SYS_JTCK-SWCLK
PA4.GPIOParameters=GPIO_Label
PA4.GPIO_Label=SPI1_CS
PA4.Signal=GPIO_Output
PA5.Signal=SPI1_SCK
PA6.Signal=SPI1_MISO
PA7.Signal=SPI1_MOSI
PB12.GPIOParameters=GPIO_Label
PB12.GPIO_Label=LED_rouge
PB12.Signal=GPIO_Output
PB13.GPIOParameters=GPIO_Label
PB13.GPIO_Label=LED_verte
PB13.Signal=GPIO_Output
PB14.GPIOParameters=GPIO_Label
PB14.GPIO_Label=LED_bleue
PB14.Signal=GPIO_Output
PB3\ (JTDO-TRACESWO).GPIOParameters=GPIO_Label
PB3\ (JTDO-TRACESWO).GPIO_Label=SWO
PB3\ (JTDO-TRACESWO).Mode=Trace_Asynchronous_SW
PB3\ (JTDO-TRACESWO).Signal=SYS_JTDO-SWO
PC10.Signal=UART4_TX
PC11.Signal=UART4_RX
PC4.Signal=GPIO_Output
PC5.Signal=GPIO_Input
PC6.Signal=GPIO_Input
PC7.Signal=GPIO_Input
PC8.Signal=GPIO_Input
PH0-OSC_IN\ (PH0).Mode=HSE-External-Oscillator
PH0-OSC_IN\ (PH0).Signal=RCC_OSC_IN
PH1-OSC_OUT\ (PH1).Mode=HSE-External-Oscillator
PH1-OSC_OUT\ (PH1).Signal=RCC_OSC_OUT
RCC.HSE_VALUE=16000000
RCC.SYSCLKFreq_VALUE=80000000
RCC.SYSCLKSource=RCC_SYSCLKSOURCE_PLLCLK
board=NUCLEO-L476RG
boardIOC=true
